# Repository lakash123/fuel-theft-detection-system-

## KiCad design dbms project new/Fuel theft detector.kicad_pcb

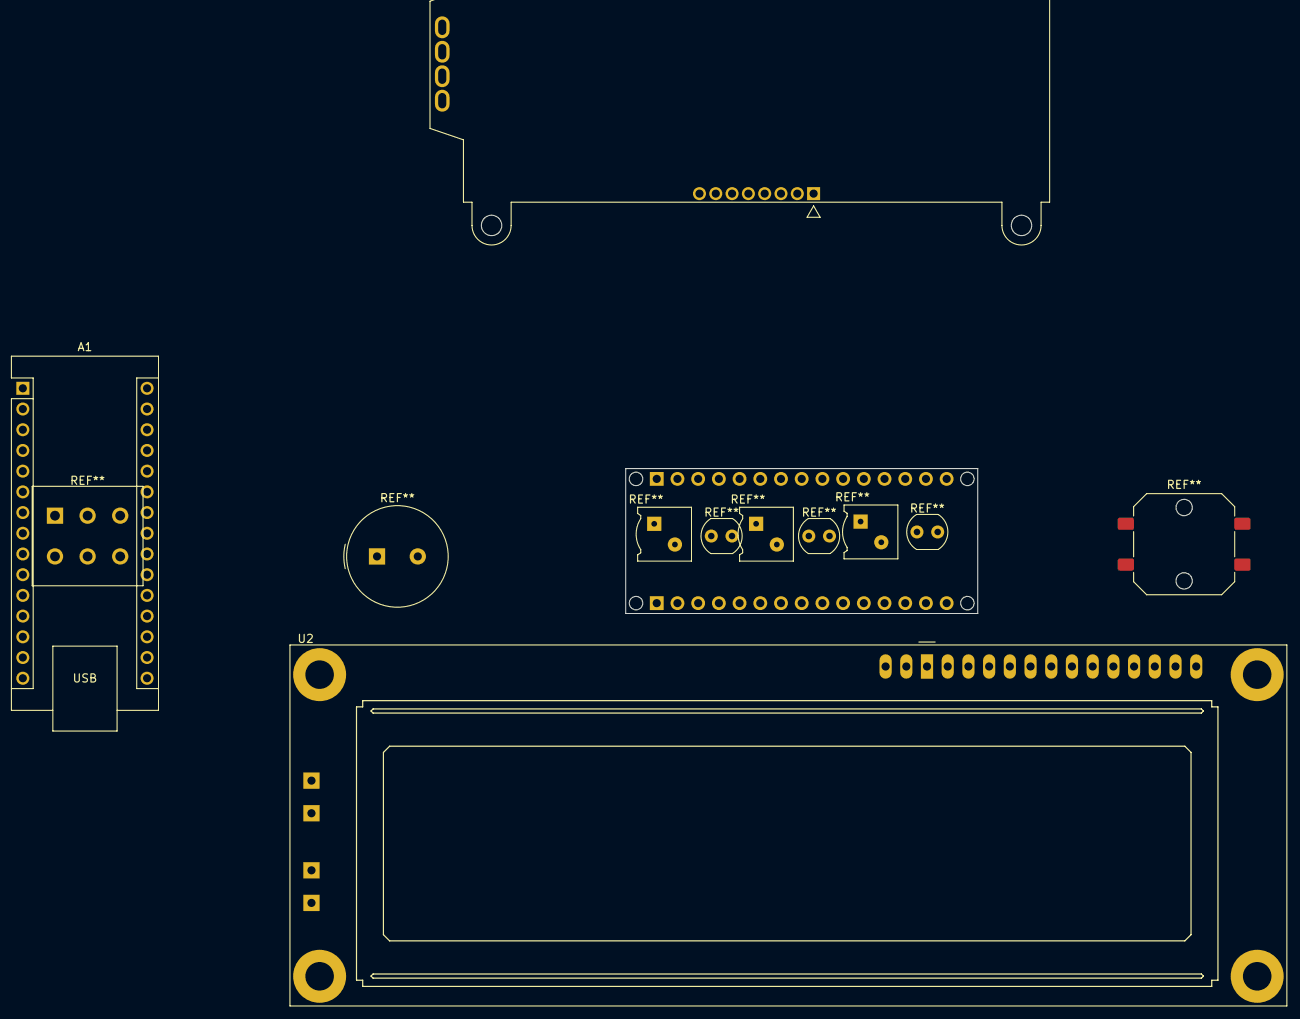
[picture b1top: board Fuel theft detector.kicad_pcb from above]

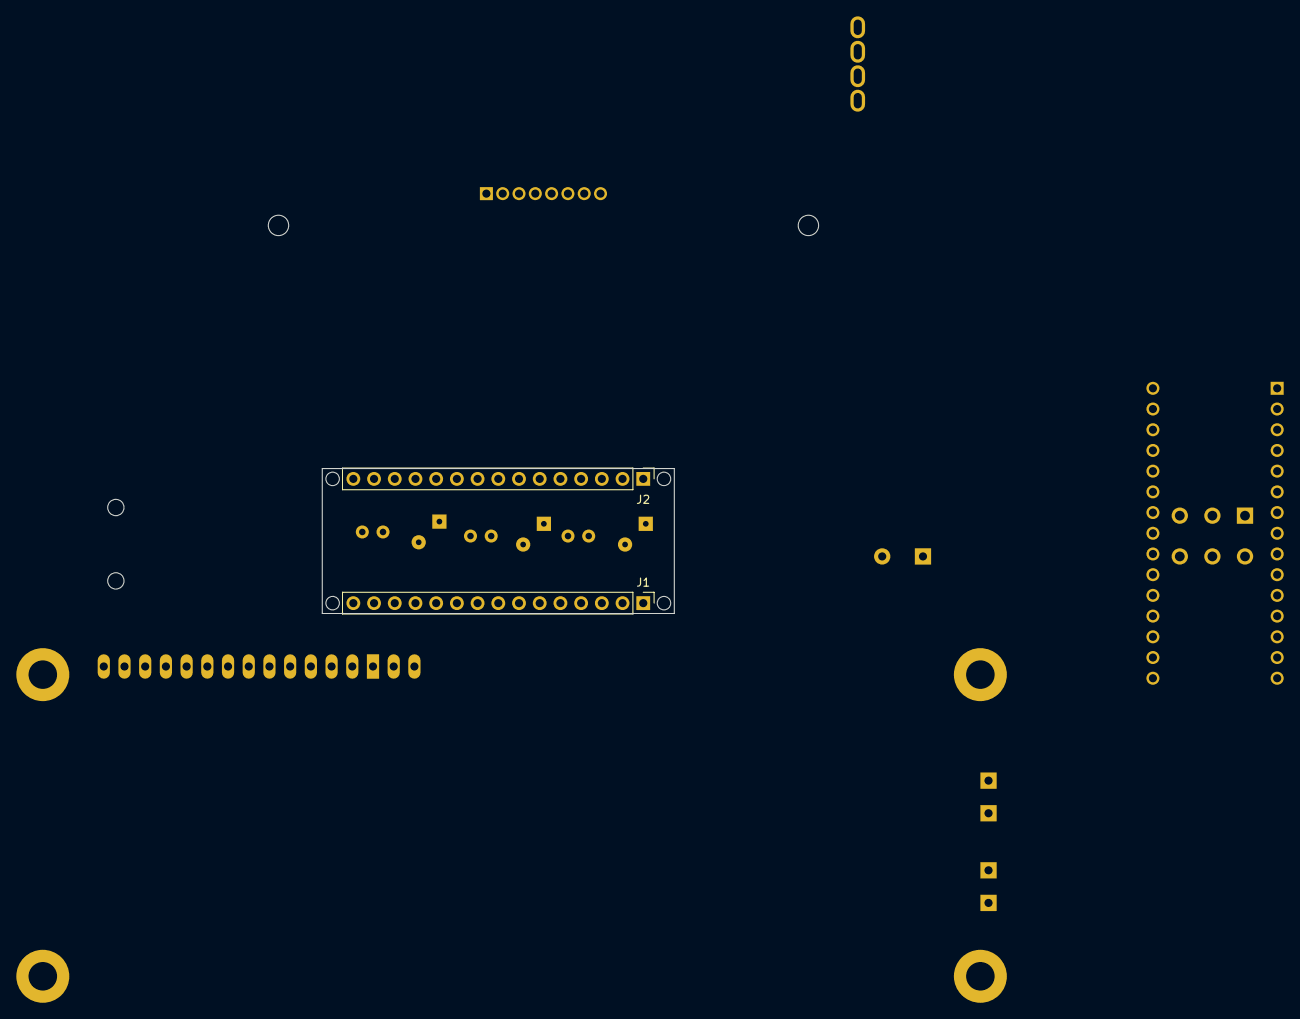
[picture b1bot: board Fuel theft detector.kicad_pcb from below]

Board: 2 copper layers, 9 parts (2 on the bottom side), 12 nets, no tracks yet.

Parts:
A1: Arduino_Nano_ESP32; Arduino_Nano
J1: Analog; PinHeader_1x15_P2.54mm_Vertical
J2: Digital; PinHeader_1x15_P2.54mm_Vertical
MH1, MH2, MH3, MH4: MountingHole_65mil
U1: NHD-C0220BIZ-FSRGB; NHD-C0220BiZ-FSRGB
U2: LCD-016N002L

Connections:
+5V: A1.13 (D10/CS), A1.27 (VUSB/5V), U1.5 (V_{DD})
/~RESET: J1.13, J2.13
GND: A1.4 (GND), A1.29 (GND), J1.14, J2.12, U1.4 (V_{SS})
unnamed: A1.19 (A0), U1.9 (LED+)
unnamed: A1.20 (A1), U1.12 ((R)LED-)
unnamed: A1.21 (A2), U1.11 ((G)LED-)
unnamed: A1.22 (A3), U1.10 ((B)LED-)
unnamed: A1.25 (A6), U1.1 (~RST)
unnamed: A1.1 (D1/TX), U1.7 (C1+)
unnamed: A1.16 (D13/SCK), U1.6 (V_{out})
unnamed: A1.24 (SCL/A5), U1.2 (SCL)
unnamed: A1.23 (SDA/A4), U1.3 (SDA)
